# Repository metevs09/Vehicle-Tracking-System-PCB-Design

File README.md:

# Vehicle-Tracking-System-PCB-Design
This design includes the schematic and board design files of a vehicle tracking system PCB.

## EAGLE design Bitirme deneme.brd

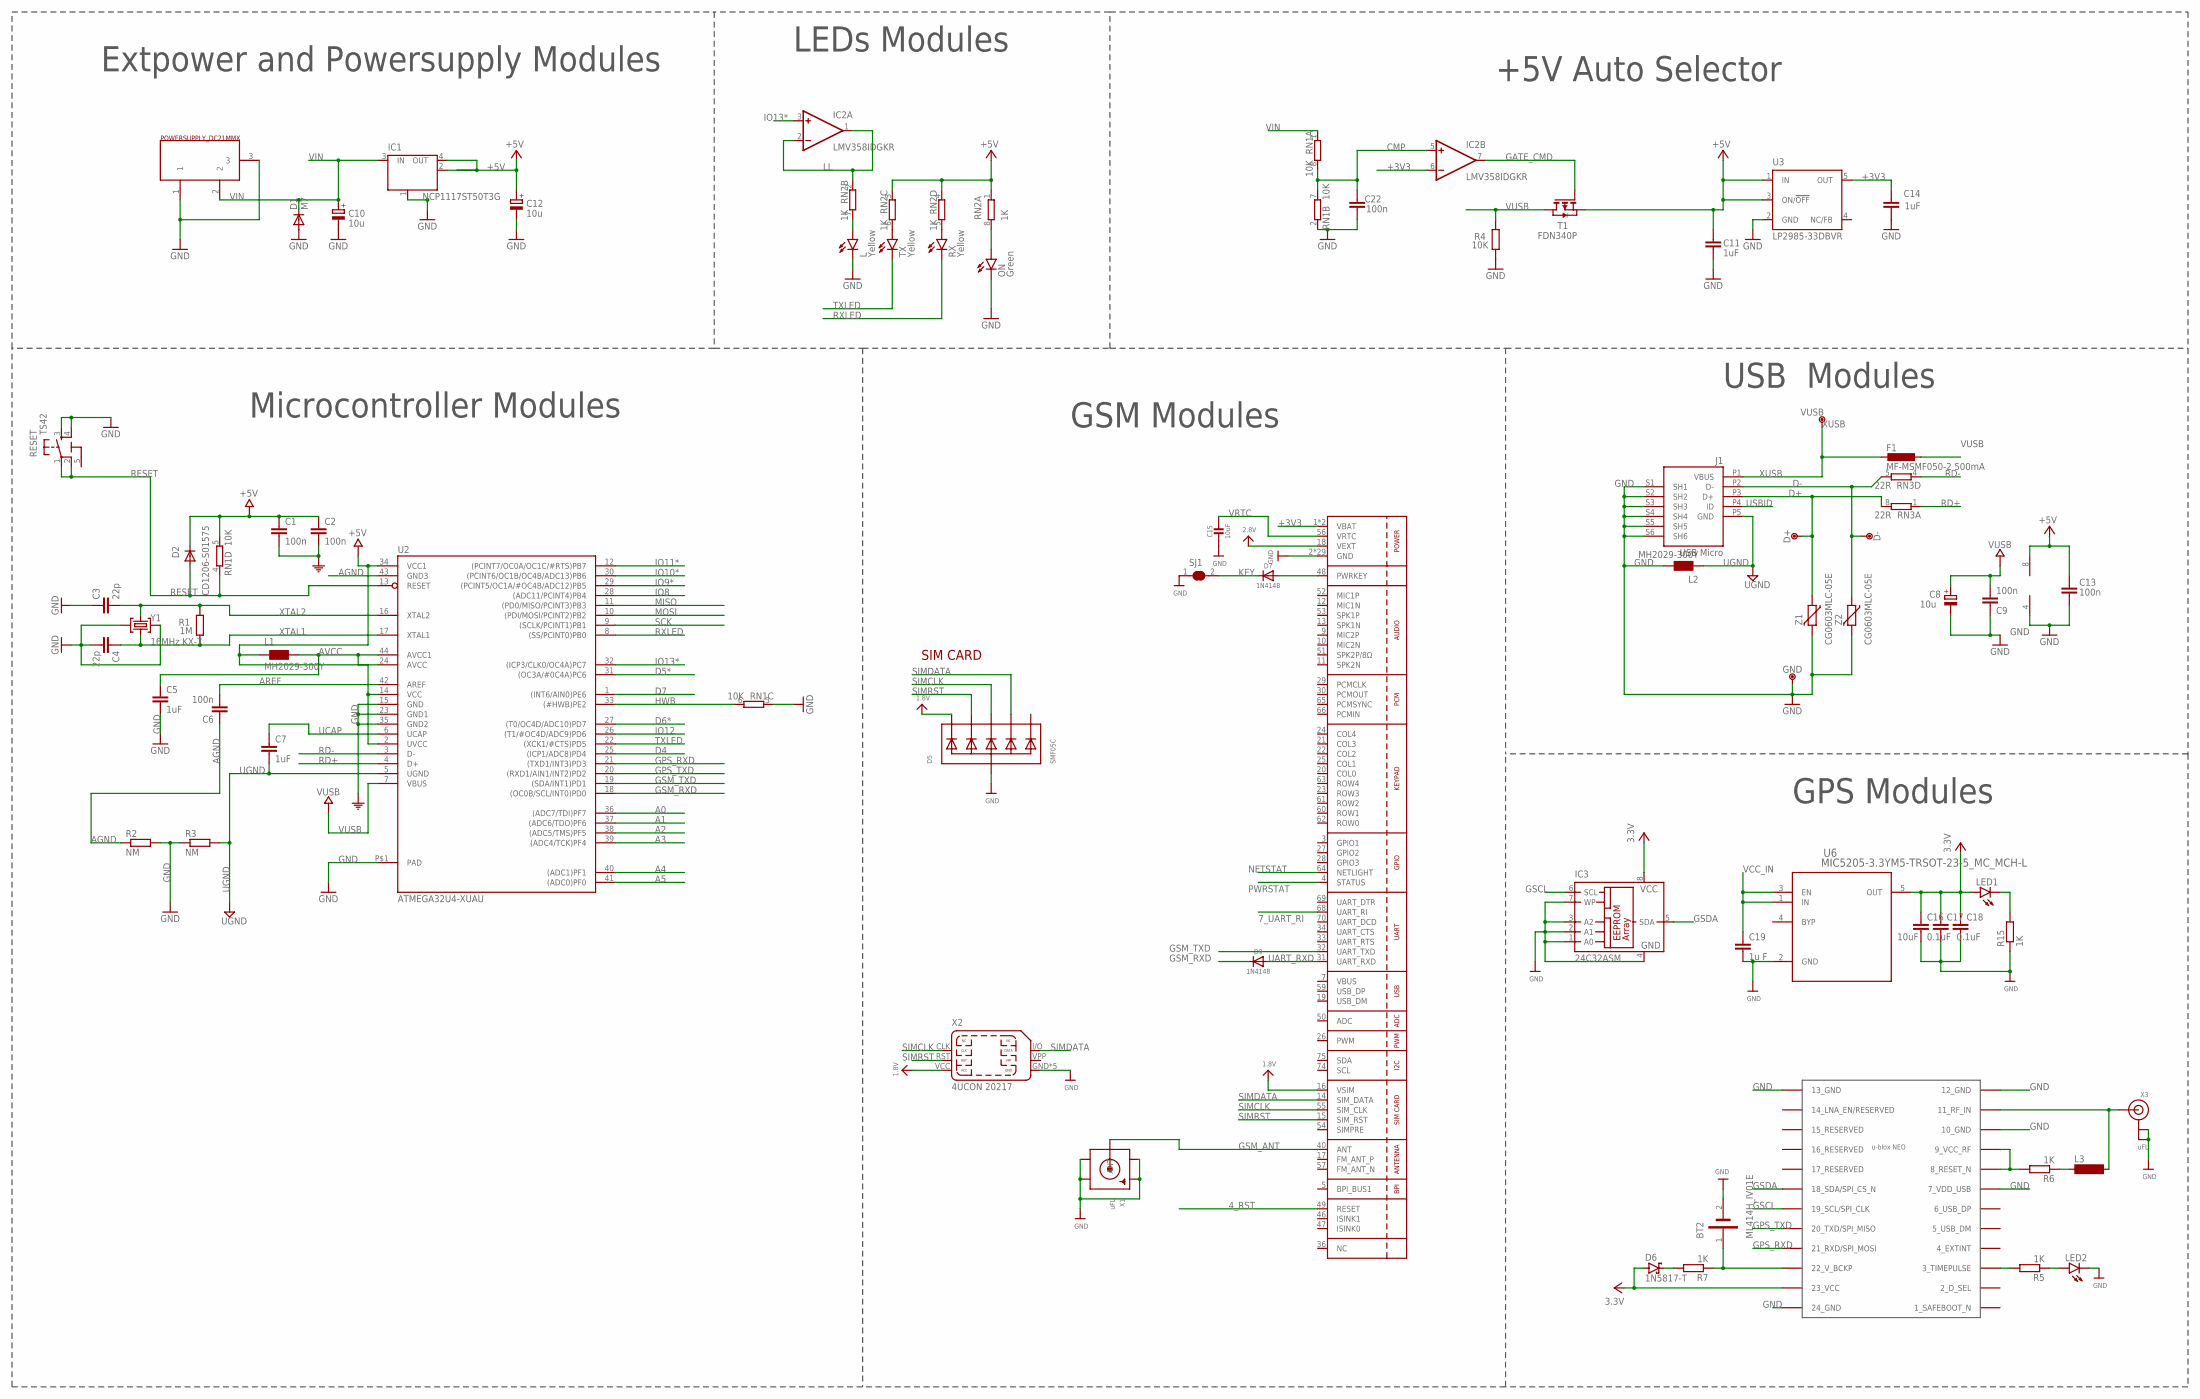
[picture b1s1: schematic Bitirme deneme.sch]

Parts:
BT2: ML414H_IV01E; SEIKO_ML414H_IV01E
C1, C2, C6, C9, C13, C22: 100n; C0603-ROUND
C3, C4: 22p; C0603-ROUND
C5, C7, C11, C14: 1uF; C0603-ROUND
C8, C10, C12: 10u; SMC_B
C15: 10uF; _0805MP
C16: 10uF; C0603K
C17, C18: 0.1uF; C0603K
C19: 1u F; C0603K
D1: M7; SMB
D2: CD1206-S01575; MINIMELF
D5: SMF05C; SOT363
D6: 1N5817-T; DO41-7.6
D7, D9: 1N4148; SOD-323
D+: DNP; TP-1.00MM
D-: DNP; TP-1.00MM
EXTPOWER: POWERSUPPLY_DC21MMX; POWERSUPPLY_DC-21MM
F1: MF-MSMF050-2 500mA; L1812
GND: DNP; TP-1.00MM
IC1: NCP1117ST50T3G; SOT223
IC2: LMV358IDGKR; MSOP08
IC3: 24C32ASM; SO-08M
J1: USB Micro; CON2_USB_MICRO_B_AT
L: Yellow; CHIPLED_0805
L1, L2: MH2029-300Y; 0805
L3: SM-1206
LED1: LEDCHIP-LED0603; CHIP-LED0603
LED2: LEDCHIPLED_1206; CHIPLED_1206
ON: Green; CHIPLED_0805
R1: 1M; R0603-ROUND
R2, R3: NM; R0402
R4: 10K; R0603-ROUND
R5, R6, R7, R15: 1K; R0402
RESET: TS42
RN1: 10K; CAY16
RN2: 1K; CAY16
RN3: 22R; CAY16
RX: Yellow; CHIPLED_0805
SJ1: SOLDERJUMPER_CLOSED; SOLDERJUMPER_CLOSEDWIRE
T1: FDN340P; SOT-23
TX: Yellow; CHIPLED_0805
U2: ATMEGA32U4-XUAU; TQFP44-PAD
U3: LP2985-33DBVR; SOT23-DBV
U4: SIM800H/L; SIM800L
U6: MIC5205-3.3YM5-TRSOT-23-5_MC_MCH-L; SOT-23-5_MC_MCH-L
U$10: NEO-M8
VUSB: DNP; TP-1.00MM
X1: uFL; SMA_EDGELAUNCH_UFL
X2: 4UCON 20217; 4UCONN_20217
X3: uFL; U.FL
Y1: 16MHz KX-7; CRYSTAL-3.2-2.5
Z1, Z2: CG0603MLC-05E; CT/CN0603

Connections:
1.8V: D5.1 (C1), U4.16 (VSIM), X2.VCC
2.8V: U4.18 (VEXT)
4_RST: U4.49 (RESET)
5-GND: RESET.5 (5-GND)
7_UART_RI: U4.68 (UART_RI)
+3V3: C14.2, IC2.6 (-IN), U3.5 (OUT), U4.1 (VBAT), U4.42 (VBAT)
+5V: C1.1, C2.1, C11.2, C12.+, C13.1, D2.C, IC1.2 (OUT), IC1.4 (OUT), IC2.8 (V+), L1.1, RN1.5 (2), RN2.1, RN2.3 (1), RN2.4 (1), T1.2 (S), U2.2 (UVCC), U2.14 (VCC), U2.34 (VCC1), U3.1 (IN), U3.3 (ON/!OFF)
A0: U2.36 ((ADC7/TDI)PF7)
A1: U2.37 ((ADC6/TDO)PF6)
A2: U2.38 ((ADC5/TMS)PF5)
A3: U2.39 ((ADC4/TCK)PF4)
A4: U2.40 ((ADC1)PF1)
A5: U2.41 ((ADC0)PF0)
AGND: C6.1, R2.1, U2.43 (GND3)
AREF: C6.2, U2.42 (AREF)
AVCC: C5.1, L1.2, U2.24 (AVCC), U2.44 (AVCC1)
CMP: C22.2, IC2.5 (+IN), RN1.7 (2), RN1.8 (2)
D4: U2.25 ((ICP1/ADC8)PD4)
D5*: U2.31 ((OC3A/#0C4A)PC6)
D6*: U2.27 ((T0/OC4D/ADC10)PD7)
D7: U2.1 ((INT6/AIN0)PE6)
D+: D+.X, J1.P3 (D+), RN3.8 (2), Z1.1
D-: D-.X, J1.P2 (D-), RN3.5 (2), Z2.1
GATE_CMD: IC2.7 (OUT), T1.3 (G)
GND: BT2.2 (NEG), C1.2, C2.2, C3.1, C4.2, C5.2, C8.-, C9.1, C10.-, C11.1, C12.-, C13.2, C14.1, C15.2, C16.2, C17.2, C18.2, C19.2, C22.1, D1.A, D5.2 (A), EXTPOWER.1, EXTPOWER.3, GND.X, IC1.1 (GND/ADJ), IC2.4 (V-), IC3.1 (A0), IC3.2 (A1), IC3.3 (A2), IC3.4 (GND), IC3.7 (WP), J1.S1 (SH1), J1.S2 (SH2), J1.S3 (SH3), J1.S4 (SH4), J1.S5 (SH5), J1.S6 (SH6), L.C, L2.2, LED2.C, ON.C, R2.2, R3.1, R4.1, R15.1, RESET.3, RESET.4, RN1.2 (1), RN1.3 (1), SJ1.1, U2.15 (GND), U2.23 (GND1), U2.35 (GND2), U2.P$1 (PAD), U3.2 (GND), U4.2 (GND), U4.6 (GND), U4.8 (GND), U4.35 (GND), U4.37 (GND), U4.38 (GND), U4.39 (GND), U4.41 (GND), U4.43 (GND), U4.44 (GND), U4.45 (GND), U4.58 (GND), U4.67 (GND), U4.71 (GND), U4.72 (GND), U4.73 (GND), U4.76 (GND), U4.77 (GND), U4.78 (GND), U4.79 (GND), U4.80 (GND), U4.81 (GND), U4.82 (GND), U4.83 (GND), U4.84 (GND), U4.85 (GND), U4.86 (GND), U4.87 (GND), U4.88 (GND), U6.2 (GND), U$10.7 (7_VDD_USB), U$10.10 (10_GND), U$10.12 (12_GND), U$10.13 (13_GND), U$10.24 (24_GND), X1.GND@1 (GND1), X1.GND@2 (GND2), X1.GND@3 (GND3), X1.GND@4 (GND4), X2.GND, X2.GND@1 (GND), X2.GND@2 (GND), X2.GND@3 (GND), X2.GND@4 (GND), X3.1 (GND), X3.2 (GND), Y1.2 (GND), Y1.4 (GND), Z1.2, Z2.2
GPS_RXD: U2.21 ((TXD1/INT3)PD3), U$10.21 (21_RXD/SPI_MOSI)
GPS_TXD: U2.20 ((RXD1/AIN1/INT2)PD2), U$10.20 (20_TXD/SPI_MISO)
GSCL: IC3.6 (SCL), U$10.19 (19_SCL/SPI_CLK)
GSDA: IC3.5 (SDA), U$10.18 (18_SDA/SPI_CS_N)
GSM_ANT: U4.40 (ANT), X1.P (ANT)
GSM_RXD: D9.C, U2.18 ((OC0B/SCL/INT0)PD0)
GSM_TXD: U2.19 ((SDA/INT1)PD1), U4.32 (UART_TXD)
HWB: RN1.6 (2), U2.33 ((#HWB)PE2)
IO8: U2.28 ((ADC11/PCINT4)PB4)
IO9*: U2.29 ((PCINT5/OC1A/#OC4B/ADC12)PB5)
IO10*: U2.30 ((PCINT6/OC1B/OC4B/ADC13)PB6)
IO11*: U2.12 ((PCINT7/OC0A/OC1C/#RTS)PB7)
IO12: U2.26 ((T1/#OC4D/ADC9)PD6)
IO13*: IC2.3 (+IN), U2.32 ((ICP3/CLK0/OC4A)PC7)
KEY: D7.C, SJ1.2
LL: IC2.1 (OUT), IC2.2 (-IN), RN2.2 (1)
MISO: U2.11 ((PD0/MISO/PCINT3)PB3)
MOSI: U2.10 ((PDI/MOSI/PCINT2)PB2)
unnamed: R5.2, U$10.3 (3_TIMEPULSE)
unnamed: LED2.A, R5.1
unnamed: R6.2, U$10.8 (8_RESET_N), U$10.9 (9_VCC_RF)
unnamed: L3.2, U$10.11 (11_RF_IN), X3.3 (SIGNAL)
unnamed: LED1.C, R15.2
unnamed: D7.A, U4.48 (PWRKEY)
unnamed: ON.A, RN2.8 (2)
unnamed: D6.C, R7.2
unnamed: L3.1, R6.1
unnamed: L.A, RN2.7 (2)
unnamed: BT2.1 (POS), R7.1, U$10.22 (22_V_BCKP)
unnamed: RN2.6 (2), TX.A
unnamed: RN2.5 (2), RX.A
NETSTAT: U4.64 (NETLIGHT)
PWRSTAT: U4.4 (STATUS)
RD+: RN3.1, U2.4 (D+)
RD-: RN3.4 (1), U2.3 (D-)
RESET: D2.A, RESET.1, RESET.2, RN1.4 (1), U2.13 (RESET)
RXLED: RX.C, U2.8 ((SS/PCINT0)PB0)
SCK: U2.9 ((SCLK/PCINT1)PB1)
SIMCLK: D5.4 (C3), U4.55 (SIM_CLK), X2.CLK
SIMDATA: D5.5 (C4), U4.14 (SIM_DATA), X2.I/O (DATA)
SIMRST: D5.3 (C2), U4.15 (SIM_RST), X2.RST
TXLED: TX.C, U2.22 ((XCK1/#CTS)PD5)
UART_RXD: D9.A, U4.31 (UART_RXD)
UCAP: C7.1, U2.6 (UCAP)
UGND: C7.2, J1.P5 (GND), L2.1, R3.2, U2.5 (UGND)
USBID: J1.P4 (ID)
VBUS: U4.7 (VBUS)
VCC: C16.1, C17.1, C18.1, D6.A, IC3.8 (VCC), LED1.A, U6.5 (OUT), U$10.23 (23_VCC)
VCC_IN: C19.1, U6.1 (IN), U6.3 (EN)
VIN: C10.+, D1.C, EXTPOWER.2, IC1.3 (IN), RN1.1
VRTC: C15.1, U4.56 (VRTC)
VUSB: C8.+, C9.2, F1.1, R4.2, T1.1 (D), U2.7 (VBUS)
XTAL1: C4.1, R1.1, U2.17 (XTAL1), Y1.1 (C1)
XTAL2: C3.2, R1.2, U2.16 (XTAL2), Y1.3 (C2)
XUSB: F1.2, J1.P1 (VBUS), VUSB.X

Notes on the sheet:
SIM CARD
GPS Modules
GSM Modules
USB Modules
+5V Auto Selector
LEDs Modules
Microcontroller Modules
Extpower and Powersupply Modules

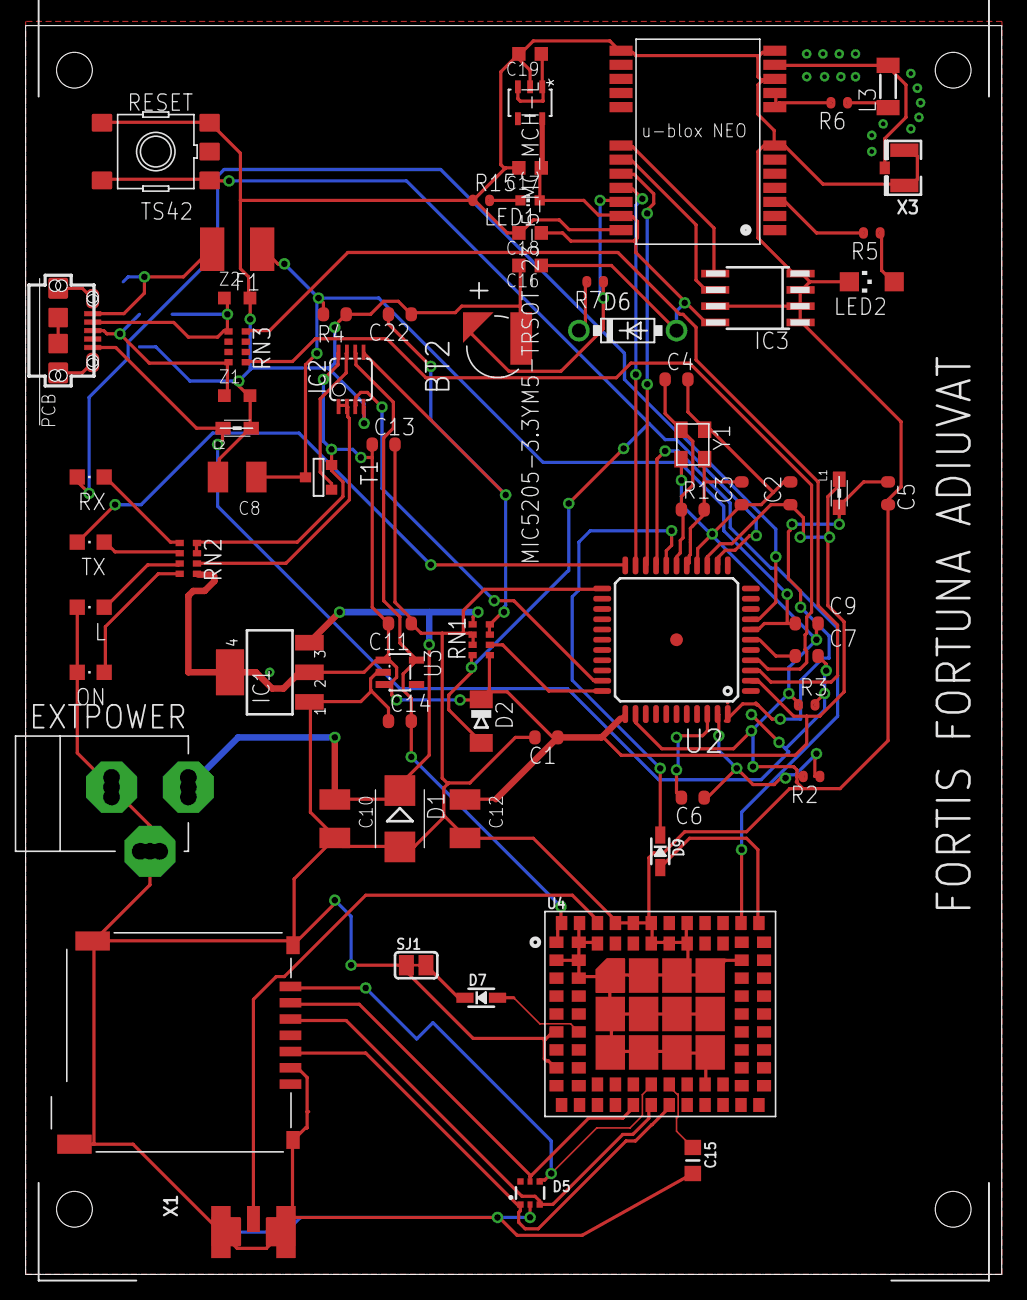
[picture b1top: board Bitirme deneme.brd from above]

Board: 2 copper layers, 76.2 x 97.5 mm, 73 parts (0 on the bottom side), 54 nets.

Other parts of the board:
U$1, U$18: BL2,8K

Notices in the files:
parts and their libraries:
microbuilder: This work is placed in the public domain, and may be freely used for commercial and non-commercial work with the following conditions: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
Arduino-utility: Copyright (c) 2016-2017 Arduino LLC.  All right reserved.
COPYRIGHT: Copyright (C) 2022 Ultra Librarian. All rights reserved.
